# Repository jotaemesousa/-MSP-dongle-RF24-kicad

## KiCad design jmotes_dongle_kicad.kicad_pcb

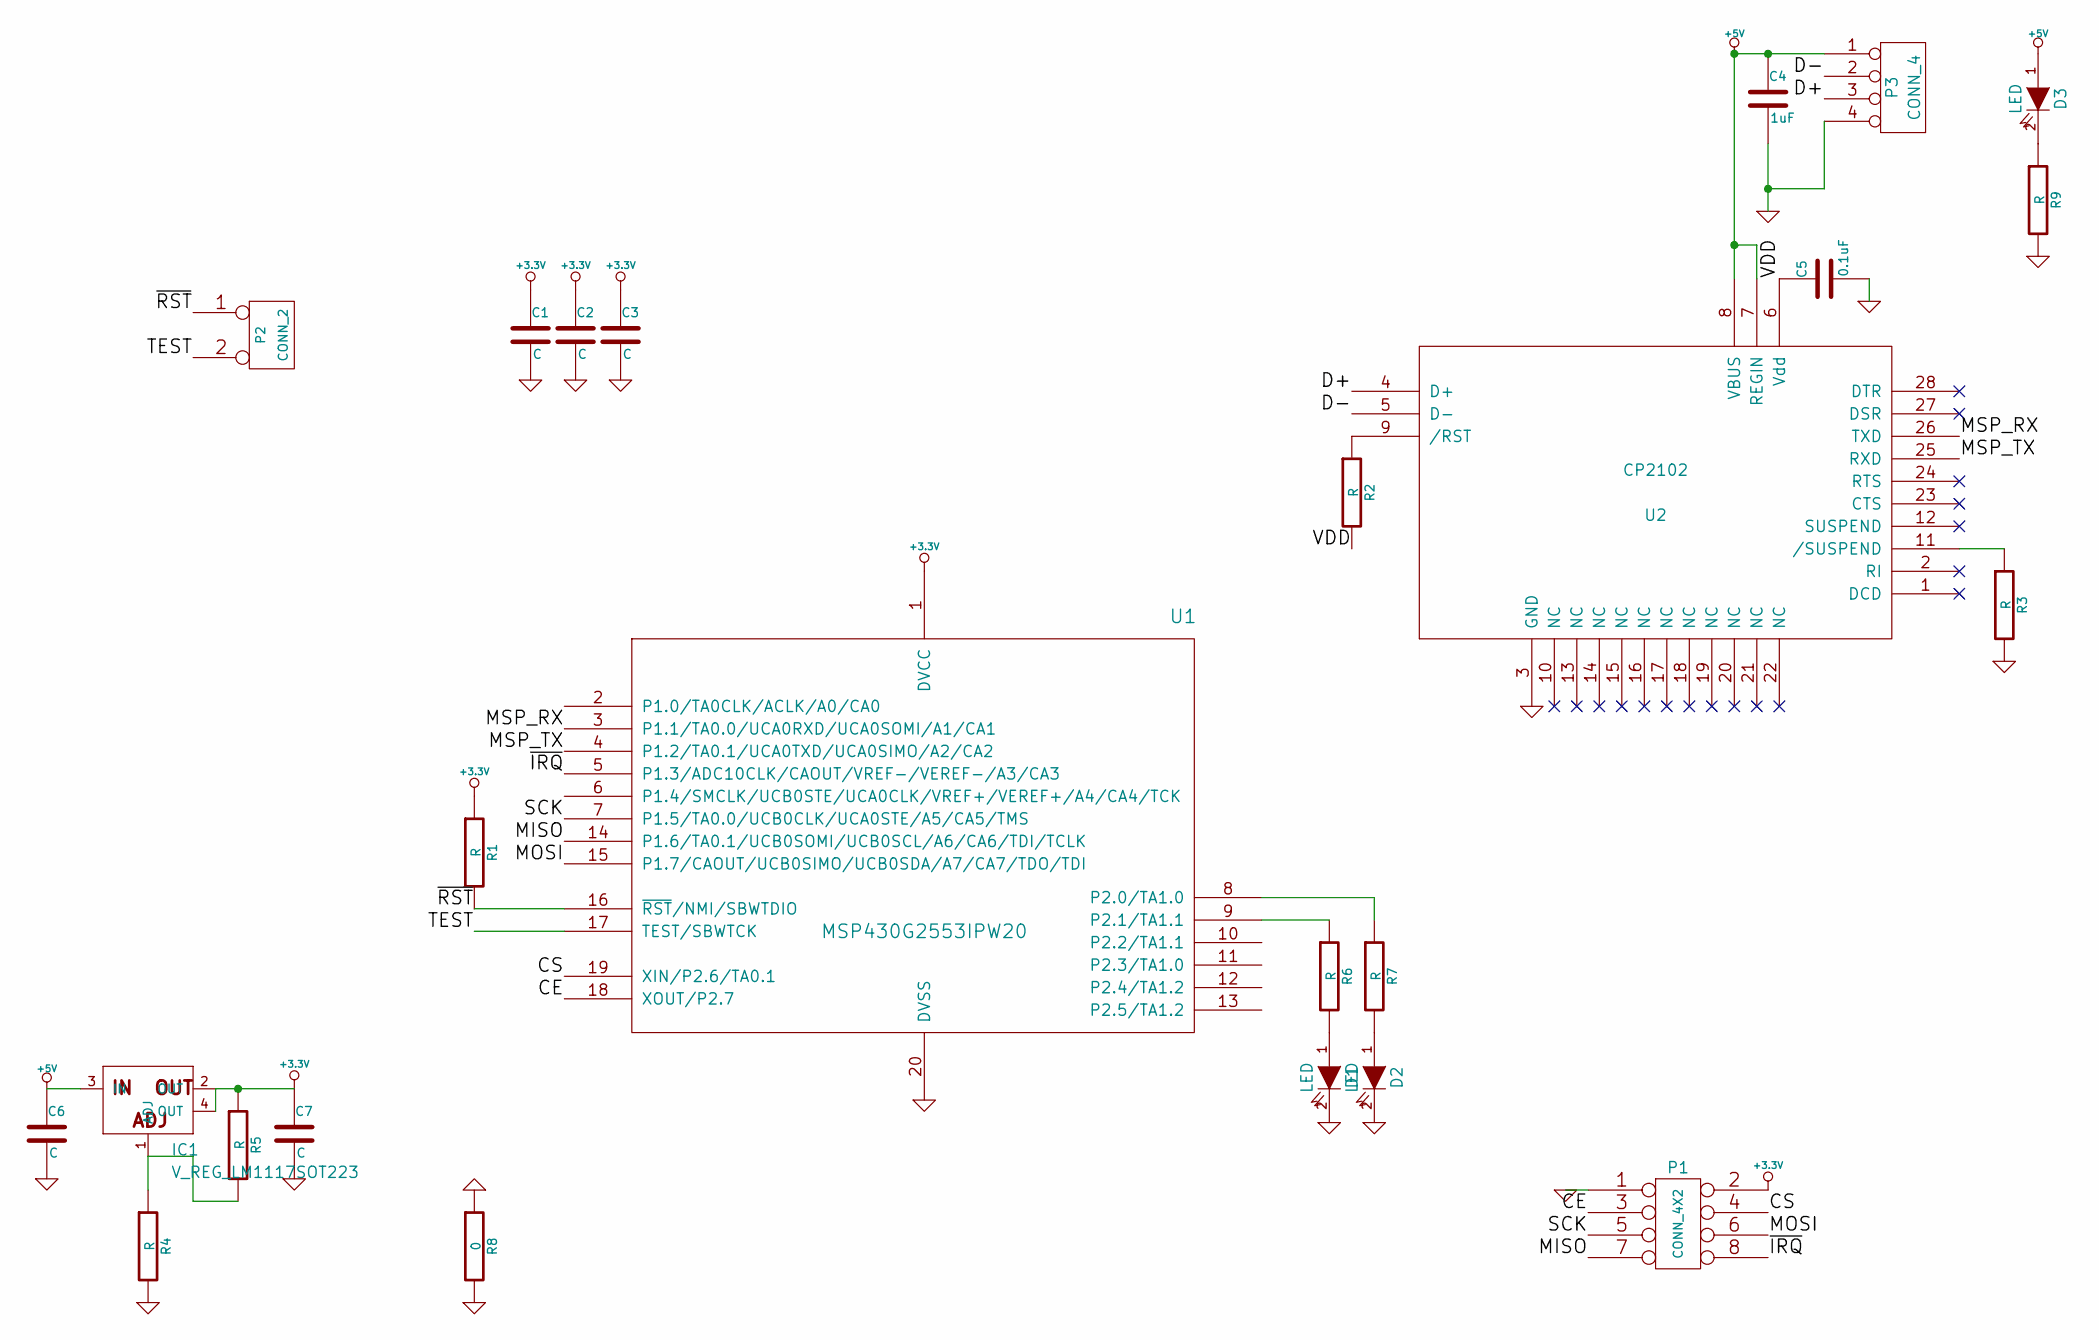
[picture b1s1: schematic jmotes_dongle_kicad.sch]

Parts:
C1, C2, C3, C6, C7: C
C4: 1uF
C5: 0.1uF
D1, D2, D3: LED
IC1: V_REG_LM1117SOT223; SparkFun-SOT223
P1: CONN_4X2
P2: CONN_2
P3: CONN_4
R1, R2, R3, R4, R5, R6, R7, R9: R
R8: 0
U1: MSP430G2553IPW20
U2: CP2102

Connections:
+3.3V: C1.1, C2.1, C3.1, C7.1, IC1.2 (OUT), IC1.4 (OUT), P1.2, R1.1, R5.1, U1.1 (DVCC)
+5V: C4.1, C6.1, D3.1 (A), IC1.3 (IN), P3.1, U2.7 (REGIN), U2.8 (VBUS)
/CE: P1.3, U1.18 (XOUT/P2.7)
/CS: P1.4, U1.19 (XIN/P2.6/TA0.1)
/D+: P3.3, U2.4 (D+)
/D-: P3.2, U2.5 (D-)
/MISO: P1.7, U1.14 (P1.6/TA0.1/UCB0SOMI/UCB0SCL/A6/CA6/TDI/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)
/MOSI: P1.6, U1.15 (P1.7/CAOUT/UCB0SIMO/UCB0SDA/A7/CA7/TDO/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)
/MSP_RX: U1.3 (P1.1/TA0.0/UCA0RXD/UCA0SOMI/A1/CA1), U2.26 (TXD)
/MSP_TX: U1.4 (P1.2/TA0.1/UCA0TXD/UCA0SIMO/A2/CA2), U2.25 (RXD)
/SCK: P1.5, U1.7 (P1.5/TA0.0/UCB0CLK/UCA0STE/A5/CA5/TMS)
/TEST: P2.2 (PM), U1.17 (TEST/SBWTCK)
/VDD: C5.1, R2.2, U2.6 (Vdd)
/~IRQ: P1.8, U1.5 (P1.3/ADC10CLK/CAOUT/VREF-/VEREF-/A3/CA3)
/~RST: P2.1, R1.2, U1.16 (~RST~/NMI/SBWTDIO)
GND: C1.2, C2.2, C3.2, C4.2, C5.2, C6.2, C7.2, D1.2 (K), D2.2 (K), P1.1, P3.4, R3.2, R4.2, R8.1, R8.2, R9.2, U1.20 (DVSS), U2.3 (GND)
unnamed: R3.1, U2.11 (/SUSPEND)
unnamed: R2.1, U2.9 (/RST)
unnamed: IC1.1 (ADJ), R4.1, R5.2
unnamed: D1.1 (A), R6.2
unnamed: D2.1 (A), R7.2
unnamed: R6.1, U1.9 (P2.1/TA1.1)
unnamed: R7.1, U1.8 (P2.0/TA1.0)
unnamed: D3.2 (K), R9.1

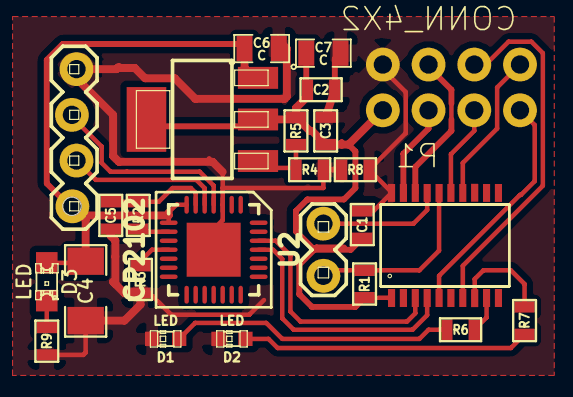
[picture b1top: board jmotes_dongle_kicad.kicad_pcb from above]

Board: 2 copper layers, 25 parts (1 on the bottom side), 24 nets.
